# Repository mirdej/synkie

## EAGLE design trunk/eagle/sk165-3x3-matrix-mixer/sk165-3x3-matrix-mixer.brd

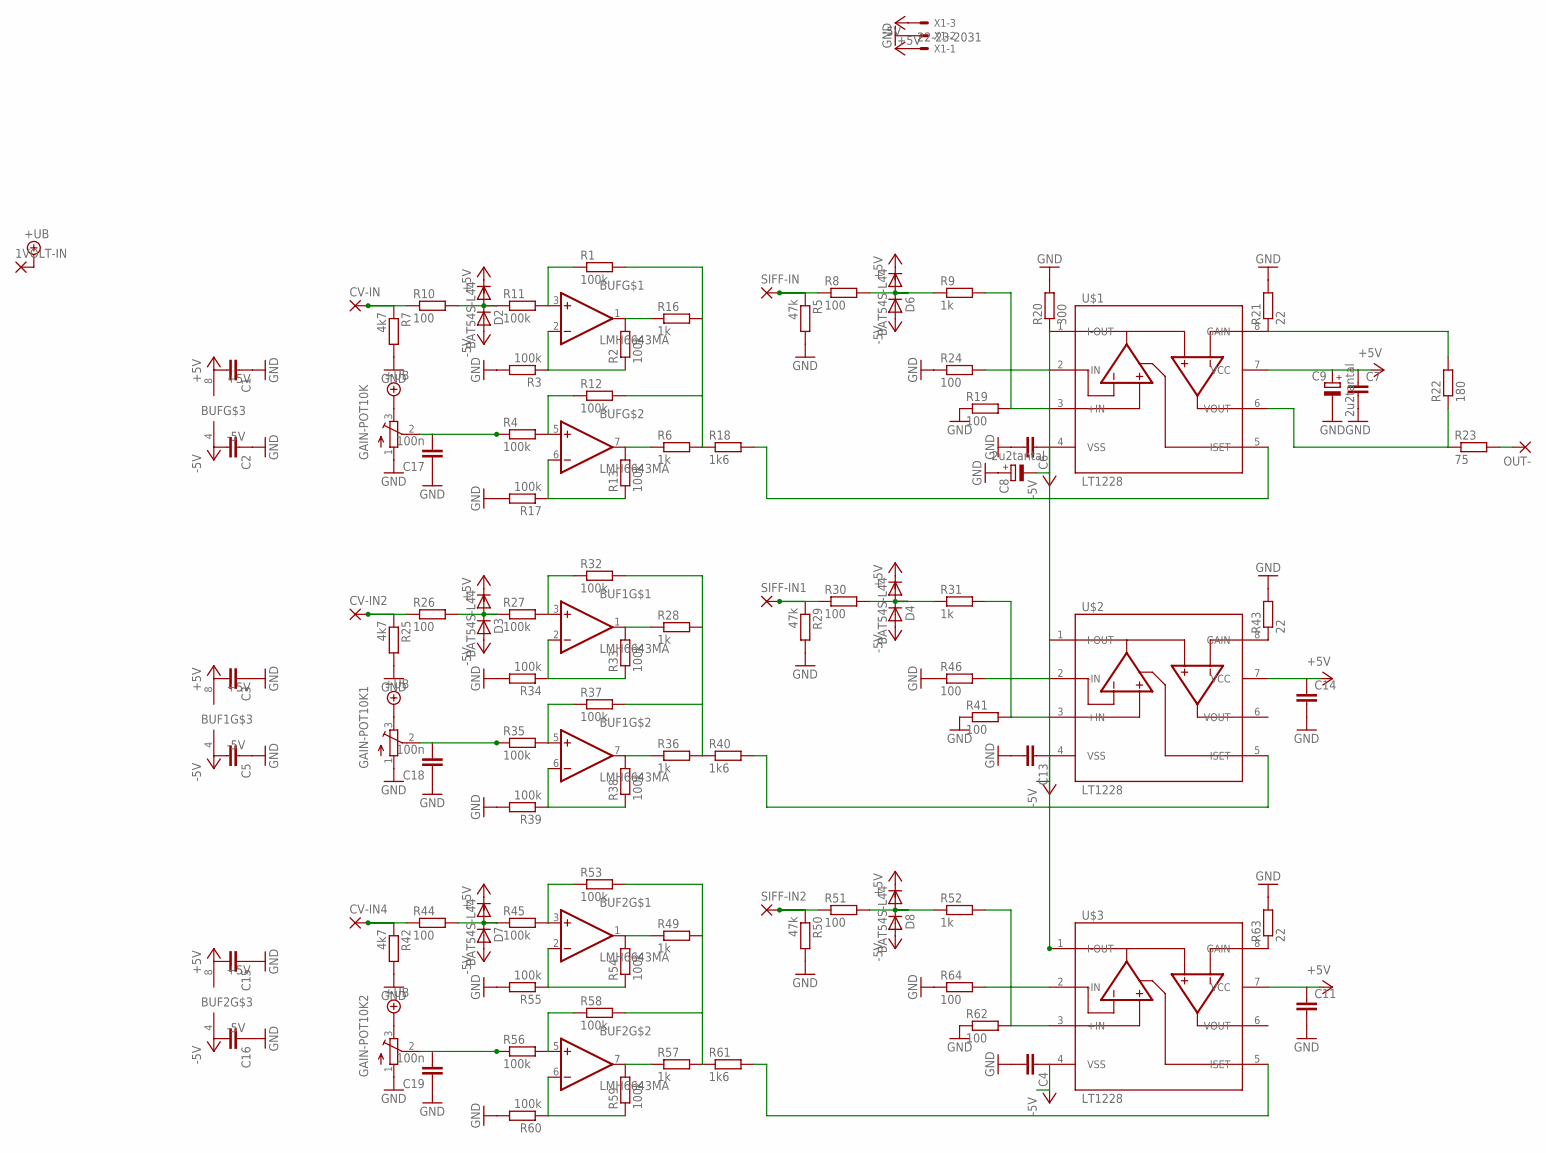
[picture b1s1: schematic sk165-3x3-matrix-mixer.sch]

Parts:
1VOLT-IN: 3,17/1,1
BUF, BUF1, BUF2: LMH6643MA; SO08
C1, C2, C3, C4, C5, C6, C7, C11, C13, C14, C15, C16: C-EUC1206; C1206
C8, C9: 2u2tantal; CT6032
C17, C18, C19: 100n; C1206
CV-IN, CV-IN2, CV-IN4: 3,17/1,1
D2, D3, D4, D6, D7, D8: BAT54S-L44; SOT23
GAIN-POT10K, GAIN-POT10K1, GAIN-POT10K2: 10k; ALPS_RK09K111
OUT-: 3,17/1,1
R1, R2, R3, R4, R11, R12, R13, R17, R27, R32, R33, R34, R35, R37, R38, R39, R45, R53, R54, R55, R56, R58, R59, R60: 100k; R1206
R5, R29, R50: 47k; R1206
R6, R9, R16, R28, R31, R36, R49, R52, R57: 1k; R1206
R7, R25, R42: 4k7; R1206
R8, R10, R19, R24, R26, R30, R41, R44, R46, R51, R62, R64: 100; R1206
R18, R40, R61: 1k6; R1206
R20: 300; R1206
R21, R43, R63: 22; R1206
R22: 180; R1206
R23: 75; R1206
SIFF-IN, SIFF-IN1, SIFF-IN2: 3,17/1,1
U$1, U$2, U$3: LT1228; SO08
X1: 22-23-2031

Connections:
+5V: BUF.8 (+5V), BUF1.8 (+5V), BUF2.8 (+5V), C1.2, C3.2, C7.1, C9.+, C11.1, C14.1, C15.2, D2.2 (C), D3.2 (C), D4.2 (C), D6.2 (C), D7.2 (C), D8.2 (C), U$1.7 (VCC), U$2.7 (VCC), U$3.7 (VCC), X1.3
+UB: 1VOLT-IN.1, GAIN-POT10K.3 (E), GAIN-POT10K1.3 (E), GAIN-POT10K2.3 (E)
-5V: BUF.4 (-5V), BUF1.4 (-5V), BUF2.4 (-5V), C2.2, C4.1, C5.2, C6.1, C8.-, C13.1, C16.2, D2.1 (A), D3.1 (A), D4.1 (A), D6.1 (A), D7.1 (A), D8.1 (A), U$1.4 (VSS), U$2.4 (VSS), U$3.4 (VSS), X1.1
GND: C1.1, C2.1, C3.1, C4.2, C5.1, C6.2, C7.2, C8.+, C9.-, C11.2, C13.2, C14.2, C15.1, C16.1, C17.1, C18.1, C19.1, GAIN-POT10K.1 (S), GAIN-POT10K1.1 (S), GAIN-POT10K2.1 (S), R3.2, R5.2, R7.2, R17.2, R19.1, R20.2, R21.2, R24.1, R25.2, R29.2, R34.2, R39.2, R41.1, R42.2, R43.2, R46.1, R50.2, R55.2, R60.2, R62.1, R63.2, R64.1, X1.2
unnamed: C17.2, GAIN-POT10K.2 (W), R4.1
unnamed: C18.2, GAIN-POT10K1.2 (W), R35.1
unnamed: CV-IN2.1, R25.1, R26.1
unnamed: BUF.2 (-IN), R2.1, R3.1
unnamed: R9.2, R19.2, U$1.3 (+IN)
unnamed: CV-IN4.1, R42.1, R44.1
unnamed: BUF.5 (+IN), R4.2, R12.1
unnamed: BUF.7 (OUT), R6.1, R13.2
unnamed: R21.1, R22.2, U$1.8 (GAIN)
unnamed: CV-IN.1, R7.1, R10.1
unnamed: D2.3 (AC), R10.2, R11.1
unnamed: BUF.6 (-IN), R13.1, R17.1
unnamed: D3.3 (AC), R26.2, R27.1
unnamed: BUF.3 (+IN), R1.1, R11.2
unnamed: R5.1, R8.1, SIFF-IN.1
unnamed: D6.3 (AC), R8.2, R9.1
unnamed: BUF.1 (OUT), R2.2, R16.1
unnamed: R18.2, U$1.5 (ISET)
unnamed: R1.2, R6.2, R12.2, R16.2, R18.1
unnamed: R22.1, R23.1, U$1.6 (VOUT)
unnamed: OUT-.1, R23.2
unnamed: R24.2, U$1.2 (-IN)
unnamed: BUF1.3 (+IN), R27.2, R32.1
unnamed: BUF1.1 (OUT), R28.1, R33.2
unnamed: R28.2, R32.2, R36.2, R37.2, R40.1
unnamed: R29.1, R30.1, SIFF-IN1.1
unnamed: D4.3 (AC), R30.2, R31.1
unnamed: R31.2, R41.2, U$2.3 (+IN)
unnamed: BUF1.2 (-IN), R33.1, R34.1
unnamed: BUF1.5 (+IN), R35.2, R37.1
unnamed: BUF1.7 (OUT), R36.1, R38.2
unnamed: BUF1.6 (-IN), R38.1, R39.1
unnamed: R40.2, U$2.5 (ISET)
unnamed: R20.1, U$1.1 (I-OUT), U$2.1 (I-OUT), U$3.1 (I-OUT)
unnamed: D7.3 (AC), R44.2, R45.1
unnamed: BUF2.3 (+IN), R45.2, R53.1
unnamed: BUF2.1 (OUT), R49.1, R54.2
unnamed: R46.2, U$2.2 (-IN)
unnamed: C19.2, GAIN-POT10K2.2 (W), R56.1
unnamed: R49.2, R53.2, R57.2, R58.2, R61.1
unnamed: R43.1, U$2.8 (GAIN)
unnamed: R50.1, R51.1, SIFF-IN2.1
unnamed: D8.3 (AC), R51.2, R52.1
unnamed: R52.2, R62.2, U$3.3 (+IN)
unnamed: BUF2.2 (-IN), R54.1, R55.1
unnamed: BUF2.5 (+IN), R56.2, R58.1
unnamed: BUF2.7 (OUT), R57.1, R59.2
unnamed: BUF2.6 (-IN), R59.1, R60.1
unnamed: R61.2, U$3.5 (ISET)
unnamed: R64.2, U$3.2 (-IN)
unnamed: R63.1, U$3.8 (GAIN)

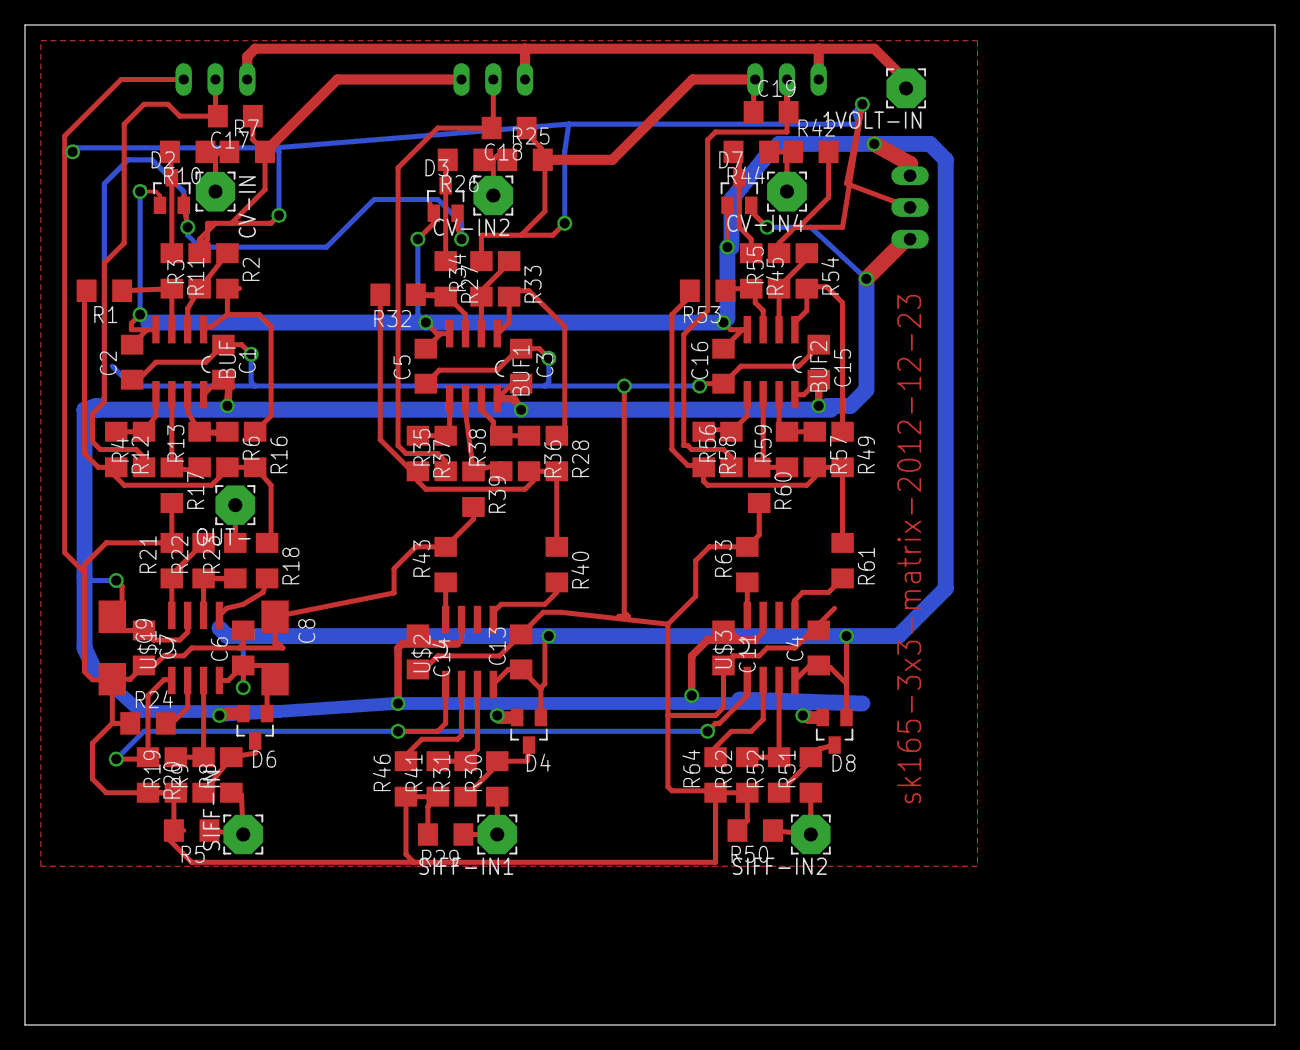
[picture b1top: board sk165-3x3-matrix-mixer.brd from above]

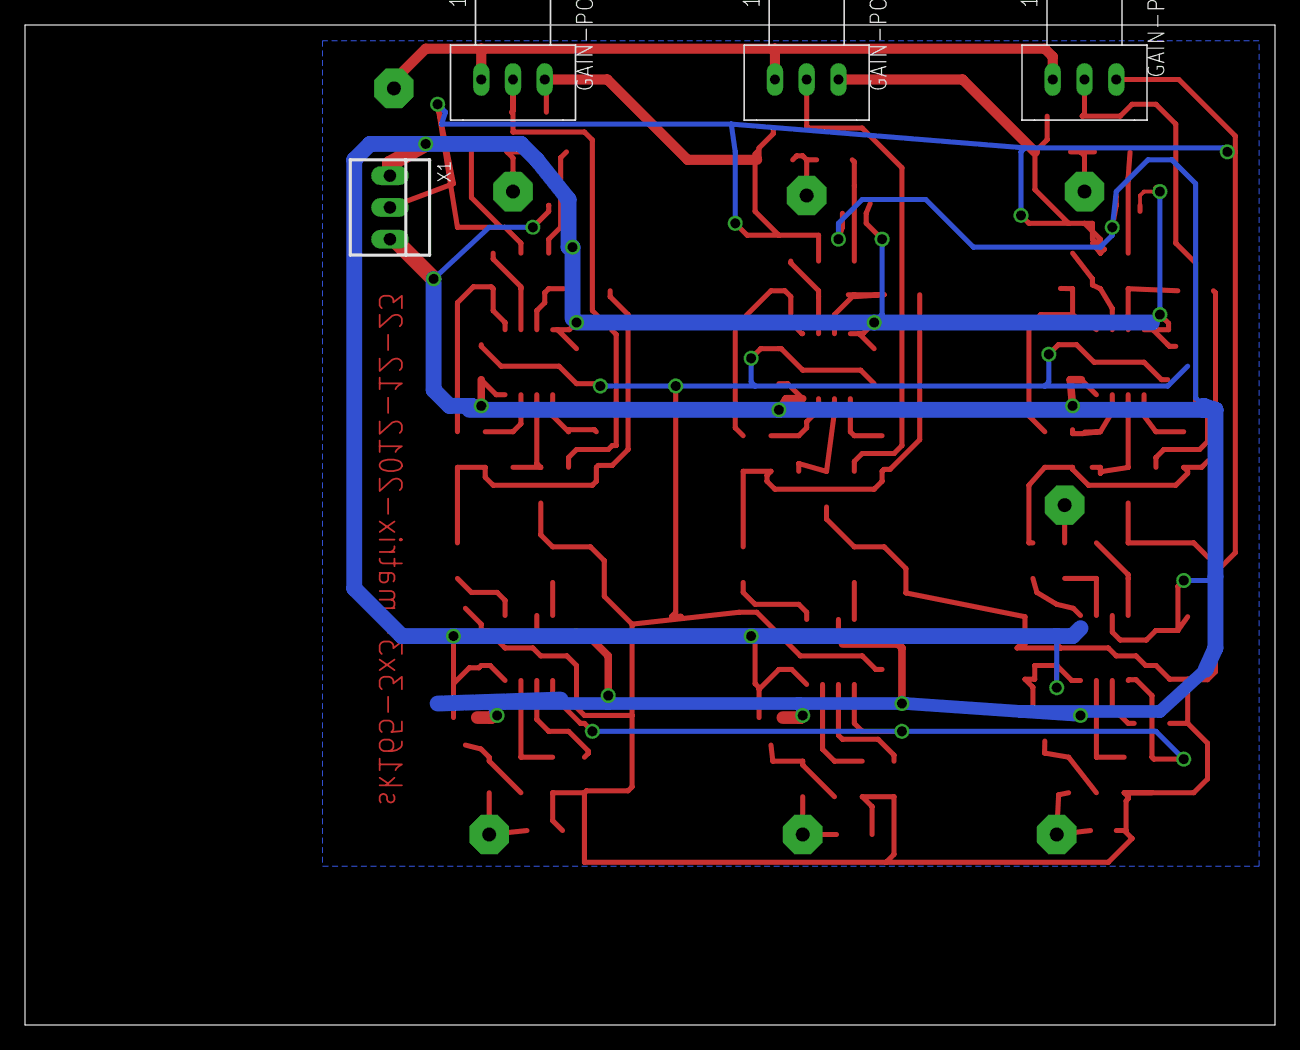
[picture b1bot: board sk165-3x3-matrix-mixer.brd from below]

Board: 2 copper layers, 100.0 x 80.0 mm, 101 parts (4 on the bottom side), 55 nets.

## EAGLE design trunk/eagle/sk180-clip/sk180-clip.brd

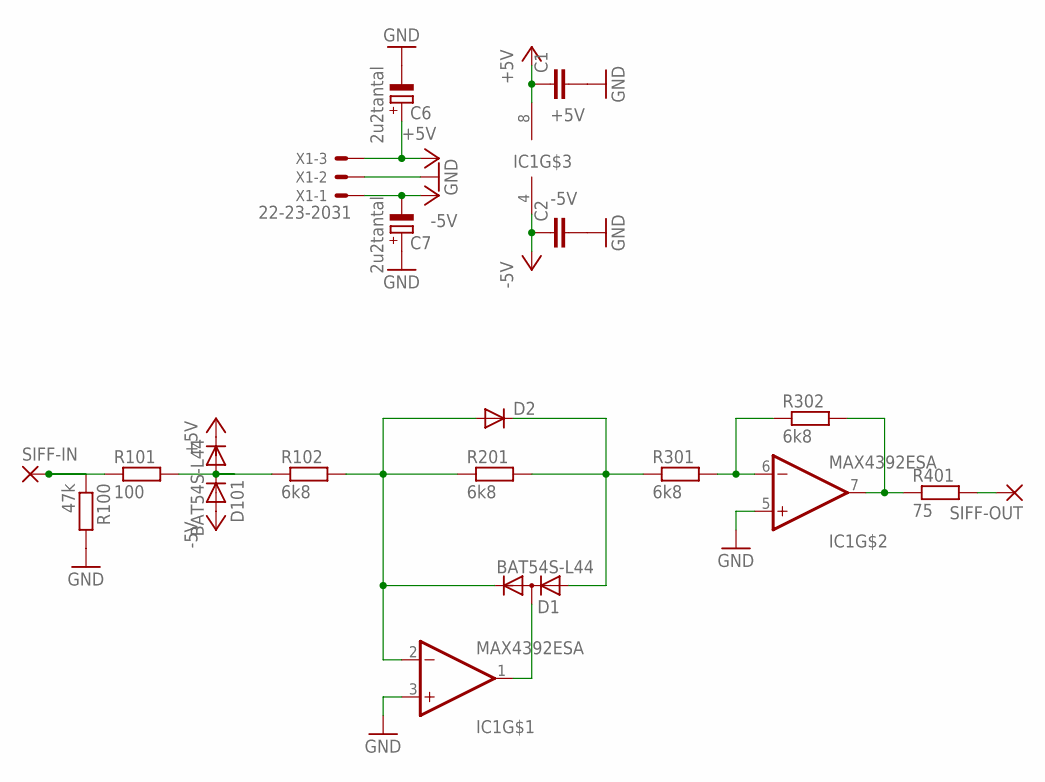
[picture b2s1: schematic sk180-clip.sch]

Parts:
C1, C2: C-EUC1206; C1206
C6, C7: 2u2tantal; CT3528
D1, D101: BAT54S-L44; SOT23
D2: DIODE-MINIMELF; MINIMELF
IC1: MAX4392ESA; SO08
R100: 47k; R1206
R101: 100; R1206
R102, R201, R301, R302: 6k8; R1206
R401: 75; R1206
SIFF-IN: 3,17/1,1
SIFF-OUT: 3,17/1,1
X1: 22-23-2031

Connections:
+5V: C1.1, C6.+, D101.2 (C), IC1.8 (+5V), X1.3
-5V: C2.1, C7.-, D101.1 (A), IC1.4 (-5V), X1.1
GND: C1.2, C2.2, C6.-, C7.+, IC1.3 (+IN), IC1.5 (+IN), R100.2, X1.2
unnamed: D1.2 (C), D2.A, IC1.2 (-IN), R102.2, R201.1
unnamed: D1.3 (AC), IC1.1 (OUT)
unnamed: D1.1 (A), D2.C, R201.2, R301.1
unnamed: IC1.6 (-IN), R301.2, R302.1
unnamed: IC1.7 (OUT), R302.2, R401.1
unnamed: R401.2, SIFF-OUT.1
unnamed: R100.1, R101.1, SIFF-IN.1
unnamed: D101.3 (AC), R101.2, R102.1

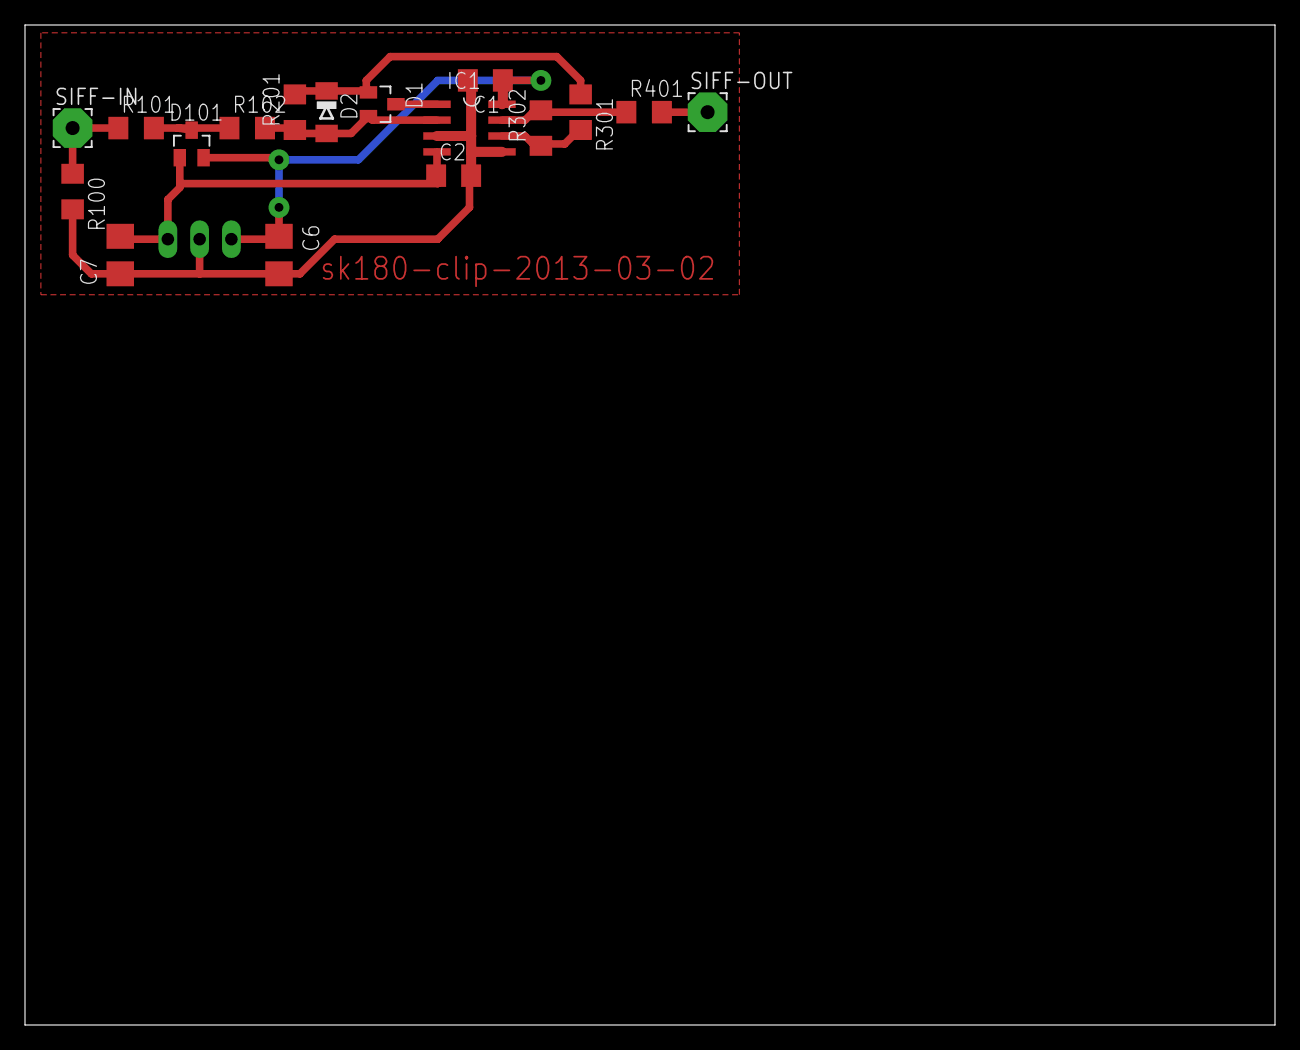
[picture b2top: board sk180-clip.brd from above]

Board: 2 copper layers, 100.0 x 80.0 mm, 18 parts (1 on the bottom side), 11 nets.

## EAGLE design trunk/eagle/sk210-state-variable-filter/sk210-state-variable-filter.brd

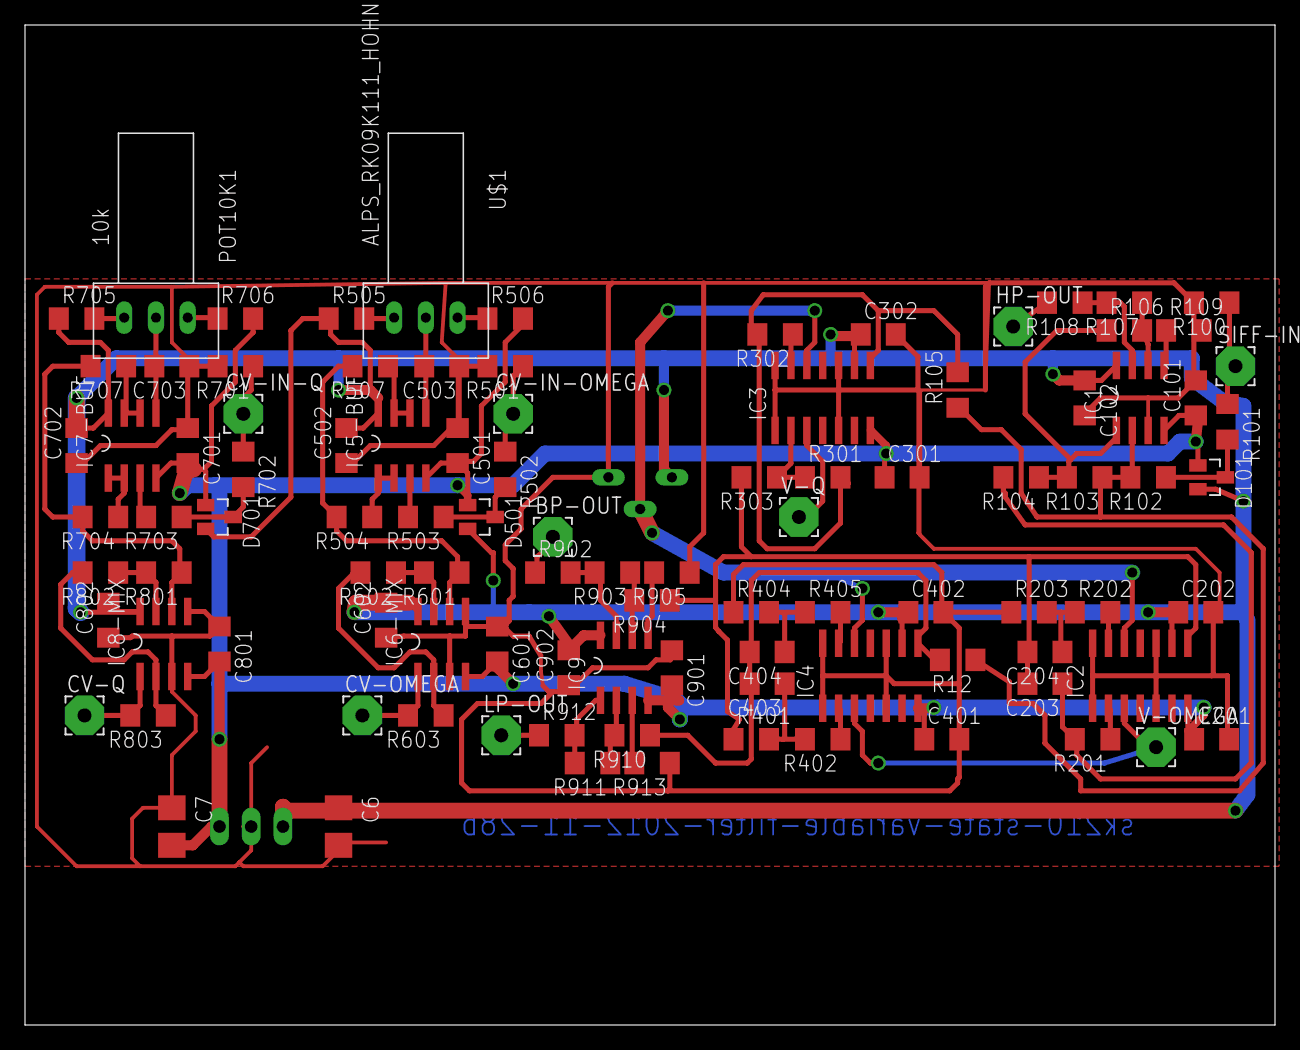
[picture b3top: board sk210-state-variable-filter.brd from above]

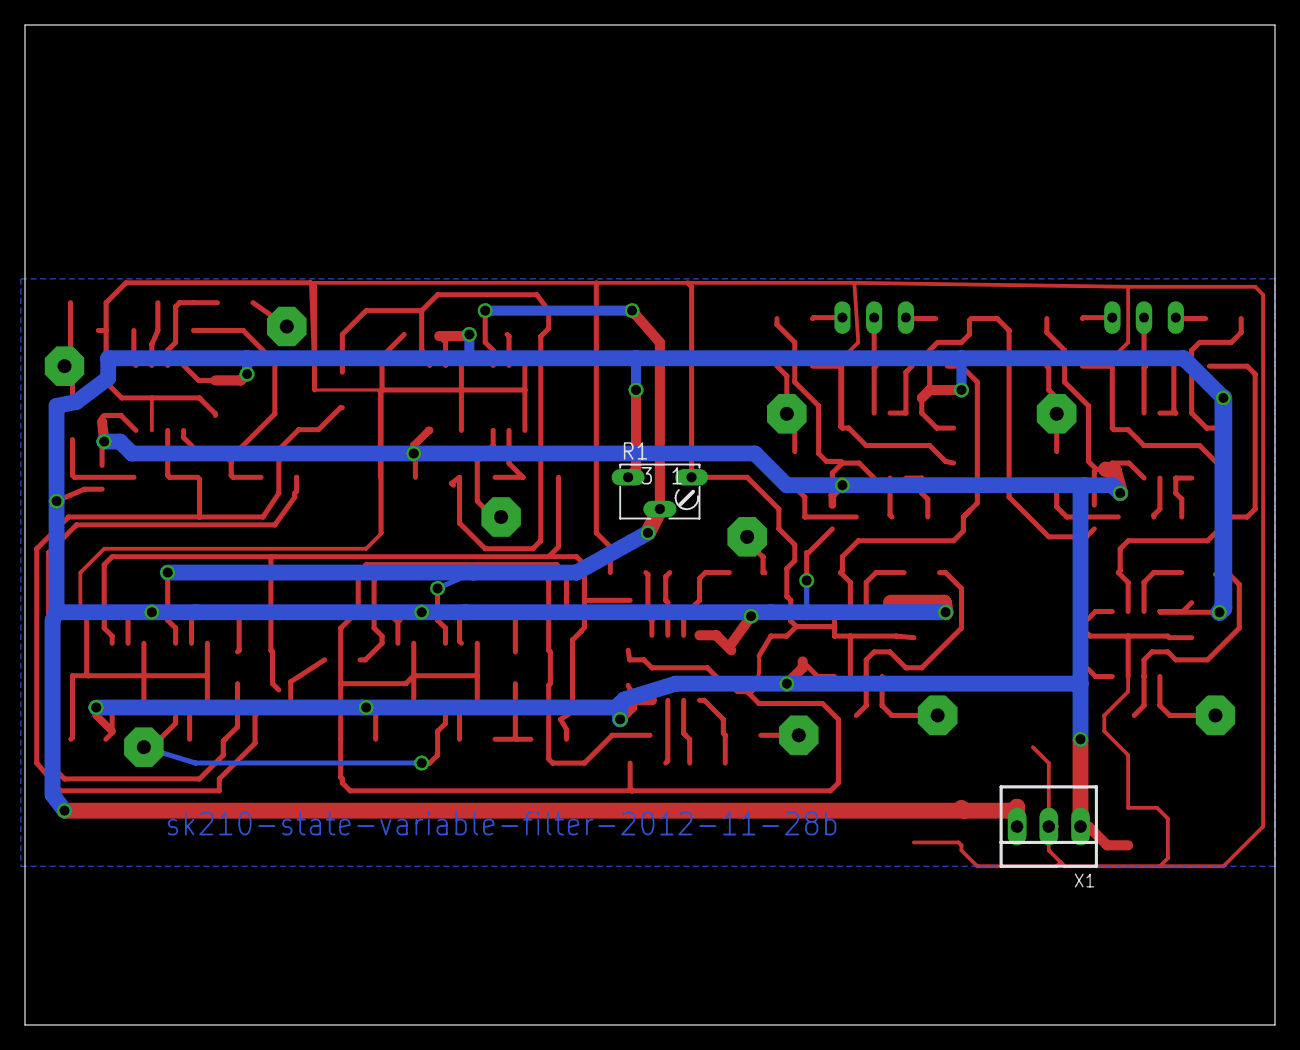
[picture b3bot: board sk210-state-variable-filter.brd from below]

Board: 2 copper layers, 100.0 x 80.0 mm, 101 parts (2 on the bottom side), 59 nets.

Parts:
BP-OUT: 3,17/1,1
C6, C7: 2u2tantal; CT3528
C101, C102, C501, C502, C601, C602, C701, C702, C801, C802, C901, C902: C1206
C201, C202, C301, C302, C401, C402, C503, C703: 100n; C1206
C203, C204, C403, C404: 120p; C1206
CV-IN-OMEGA: 3,17/1,1
CV-IN-Q: 3,17/1,1
CV-OMEGA: 3,17/1,1
CV-Q: 3,17/1,1
D101, D501, D701: BAT54S-L44; SOT23
HP-OUT: 3,17/1,1
IC1, IC5-BUF, IC6-MIX, IC7-BUF, IC8-MIX, IC9: MAX4392ESA; SO08
IC2, IC3, IC4: LT1256; SO14
LP-OUT: 3,17/1,1
POT10K1: 10k; ALPS_RK09K111
R1: B64W
R12, R102, R103, R104, R106, R107, R203, R401, R404, R903, R904, R910, R911: 1k; R1206
R100, R501, R701: 47k; R1206
R101, R502, R503, R702, R703: 100; R1206
R105, R109, R905, R913: 500; R1206
R108, R902, R912: 75; R1206
R201, R202, R301, R302, R303, R402, R405: 1k5; R1206
R504, R507, R601, R602, R603, R704, R707, R801, R802, R803: 6k8; R1206
R505, R506, R705, R706: 20k; R1206
SIFF-IN: 3,17/1,1
U$1: ALPS_RK09K111_HOHNE-FüSSE; ALPS_RK09K111
V-OMEGA: 3,17/1,1
V-Q: 3,17/1,1
X1: 22-23-2031

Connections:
+5V: C6.+, C102.1, C202.1, C302.1, C402.1, C502.2, C602.2, C702.2, C802.2, C902.2, D101.2, D501.2, D701.2, IC1.8, IC2.9, IC3.9, IC4.9, IC5-BUF.8, IC6-MIX.8, IC7-BUF.8, IC8-MIX.8, IC9.8, R1.E, R505.1, R705.1, X1.3
+UB: IC2.12, IC3.12, IC4.12, R1.S
-5V: C7.-, C101.1, C201.1, C301.1, C401.1, C501.2, C601.2, C701.2, C801.2, C901.2, D101.1, D501.1, D701.1, IC1.4, IC2.7, IC3.7, IC4.7, IC5-BUF.4, IC6-MIX.4, IC7-BUF.4, IC8-MIX.4, IC9.4, R506.2, R706.2, X1.1
GND: C6.-, C7.+, C101.2, C102.2, C201.2, C202.2, C301.2, C302.2, C401.2, C402.2, C501.1, C502.1, C503.1, C601.1, C602.1, C701.1, C702.1, C703.1, C801.1, C802.1, C901.1, C902.1, IC1.3, IC2.1, IC2.5, IC2.10, IC2.14, IC3.1, IC3.5, IC3.10, IC3.14, IC4.1, IC4.5, IC4.10, IC4.14, IC6-MIX.3, IC6-MIX.5, IC8-MIX.3, IC8-MIX.5, R1.A, R100.2, R109.2, R203.1, R404.1, R501.2, R701.2, R905.1, R913.1, X1.2
unnamed: C503.2, IC5-BUF.5, U$1.2
unnamed: R506.1, U$1.1
unnamed: R505.2, U$1.3
unnamed: IC1.7, R107.2, R108.1
unnamed: IC1.2, R12.1, R102.2, R103.1, R105.1
unnamed: C203.1, R104.2, R201.2
unnamed: C203.2, C204.2, IC2.8, R303.2, R401.1, R904.1
unnamed: IC3.2, R301.1, R303.1
unnamed: IC3.8, R105.2, R301.2, R302.2
unnamed: CV-IN-OMEGA.1, R501.1, R502.1
unnamed: D501.3, R502.2, R503.1
unnamed: IC2.2, R201.1
unnamed: IC5-BUF.6, IC5-BUF.7, R507.1
unnamed: IC5-BUF.3, R503.2
unnamed: R100.1, R101.1, SIFF-IN.1
unnamed: D101.3, R101.2, R102.1
unnamed: IC5-BUF.1, IC5-BUF.2, R504.1
unnamed: IC3.13, R302.1
unnamed: IC6-MIX.6, R504.2, R507.2, R601.1
unnamed: IC6-MIX.7, R601.2, R602.1
unnamed: IC6-MIX.2, R602.2, R603.1
unnamed: CV-OMEGA.1, IC6-MIX.1, R603.2
unnamed: IC3.3, V-Q.1
unnamed: IC2.3, IC4.3, V-OMEGA.1
unnamed: CV-IN-Q.1, R701.1, R702.1
unnamed: IC2.13, R202.2
unnamed: C204.1, R202.1, R203.2
unnamed: C403.1, R401.2, R402.2
unnamed: C403.2, C404.2, IC4.8, R12.2, R910.1
unnamed: IC4.2, R402.1
unnamed: D701.3, R702.2, R703.1
unnamed: C404.1, R404.2, R405.1
unnamed: IC7-BUF.3, R703.2
unnamed: IC7-BUF.1, IC7-BUF.2, R704.1
unnamed: IC7-BUF.6, IC7-BUF.7, R707.1
unnamed: IC8-MIX.6, R704.2, R707.2, R801.1
unnamed: IC8-MIX.7, R801.2, R802.1
unnamed: IC8-MIX.2, R802.2, R803.1
unnamed: CV-Q.1, IC8-MIX.1, R803.2
unnamed: C703.2, IC7-BUF.5, POT10K1.2
unnamed: POT10K1.1, R706.1
unnamed: POT10K1.3, R705.2
unnamed: IC9.1, R911.2, R912.2
unnamed: HP-OUT.1, R108.2
unnamed: IC9.7, R902.2, R903.2
unnamed: IC1.1, R103.2, R104.1, R106.1
unnamed: LP-OUT.1, R912.1
unnamed: BP-OUT.1, R902.1
unnamed: IC9.6, R903.1, R904.2
unnamed: IC9.5, R905.2
unnamed: IC1.6, R106.2, R107.1
unnamed: IC1.5, R109.1
unnamed: IC9.2, R910.2, R911.1
unnamed: IC9.3, R913.2
R403: IC4.13, R405.2

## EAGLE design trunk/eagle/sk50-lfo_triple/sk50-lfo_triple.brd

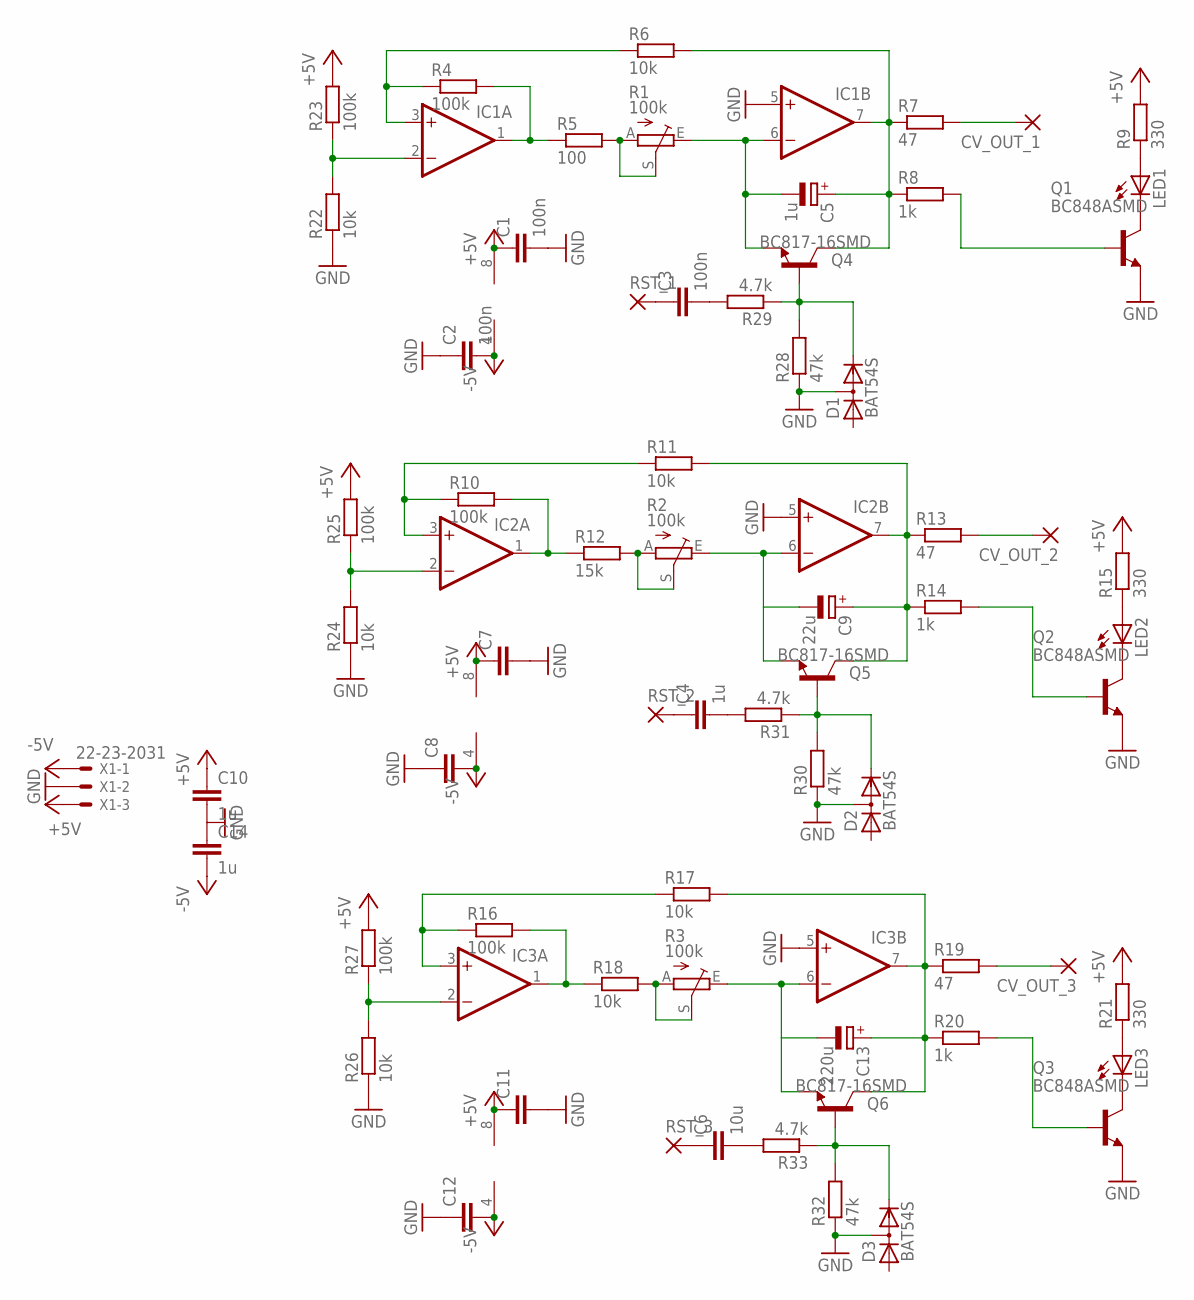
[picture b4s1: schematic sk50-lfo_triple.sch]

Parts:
C1, C2, C3: 100n; C1206
C4, C10, C14: 1u; C1206
C5: 1u; E2,5-5
C6: 10u; C1206
C7, C8, C11, C12: C-EUC1206; C1206
C9: 22u; E2,5-5
C13: 220u; E2,5-5
CV_OUT_1, CV_OUT_2, CV_OUT_3: 3,17/1,1
D1, D2, D3: BAT54S; SOT23
IC1, IC2, IC3: 2AMP_P8+4D; SO08
LED1, LED2, LED3: LED3MM
Q1, Q2, Q3: BC848ASMD; SOT23
Q4, Q5, Q6: BC817-16SMD; SOT23-BEC
R1, R2, R3: 100k; CIP20C-6MM
R4, R10, R16, R23, R25, R27: 100k; R1206
R5: 100; R1206
R6, R11, R17, R18, R22, R24, R26: 10k; R1206
R7, R13, R19: 47; R1206
R8, R14, R20: 1k; R1206
R9, R15, R21: 330; R1206
R12: 15k; R1206
R28, R30, R32: 47k; R1206
R29, R31, R33: 4.7k; R1206
RST_1, RST_2, RST_3: 3,17/1,1
X1: 22-23-2031

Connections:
+5V: C1.1, C7.1, C10.1, C11.1, IC1.8 (V+), IC2.8 (V+), IC3.8 (V+), R9.2, R15.2, R21.2, R23.2, R25.2, R27.2, X1.3
-5V: C2.2, C8.2, C12.2, C14.2, IC1.4 (V-), IC2.4 (V-), IC3.4 (V-), X1.1
GND: C1.2, C2.1, C7.2, C8.1, C10.2, C11.2, C12.1, C14.1, D1.3 (AC), D2.3 (AC), D3.3 (AC), IC1.5 (+IN), IC2.5 (+IN), IC3.5 (+IN), Q1.2 (E), Q2.2 (E), Q3.2 (E), R22.1, R24.1, R26.1, R28.1, R30.1, R32.1, X1.2
unnamed: IC1.3 (+IN), R4.1, R6.1
unnamed: IC1.1 (OUT), R4.2, R5.1
unnamed: R1.A, R1.S, R5.2
unnamed: C5.-, IC1.6 (-IN), Q4.E, R1.E
unnamed: C5.+, IC1.7 (OUT), Q4.C, R6.2, R7.1, R8.1
unnamed: LED2.A, R15.1
unnamed: CV_OUT_1.1, R7.2
unnamed: Q1.1 (B), R8.2
unnamed: LED1.A, R9.1
unnamed: LED1.K (C), Q1.3 (C)
unnamed: IC2.3 (+IN), R10.1, R11.1
unnamed: IC2.1 (OUT), R10.2, R12.1
unnamed: R2.A, R2.S, R12.2
unnamed: C9.-, IC2.6 (-IN), Q5.E, R2.E
unnamed: C9.+, IC2.7 (OUT), Q5.C, R11.2, R13.1, R14.1
unnamed: LED2.K (C), Q2.3 (C)
unnamed: CV_OUT_2.1, R13.2
unnamed: Q2.1 (B), R14.2
unnamed: LED3.A, R21.1
unnamed: LED3.K (C), Q3.3 (C)
unnamed: IC3.3 (+IN), R16.1, R17.1
unnamed: IC3.1 (OUT), R16.2, R18.1
unnamed: R3.A, R3.S, R18.2
unnamed: C13.-, IC3.6 (-IN), Q6.E, R3.E
unnamed: C13.+, IC3.7 (OUT), Q6.C, R17.2, R19.1, R20.1
unnamed: Q3.1 (B), R20.2
unnamed: CV_OUT_3.1, R19.2
unnamed: IC1.2 (-IN), R22.2, R23.1
unnamed: IC2.2 (-IN), R24.2, R25.1
unnamed: IC3.2 (-IN), R26.2, R27.1
unnamed: C3.2, R29.2
unnamed: C3.1, RST_1.1
unnamed: D2.2 (C), Q5.B, R30.2, R31.1
unnamed: D1.2 (C), Q4.B, R28.2, R29.1
unnamed: C4.2, R31.2
unnamed: C6.2, R33.2
unnamed: C4.1, RST_2.1
unnamed: C6.1, RST_3.1
unnamed: D3.2 (C), Q6.B, R32.2, R33.1

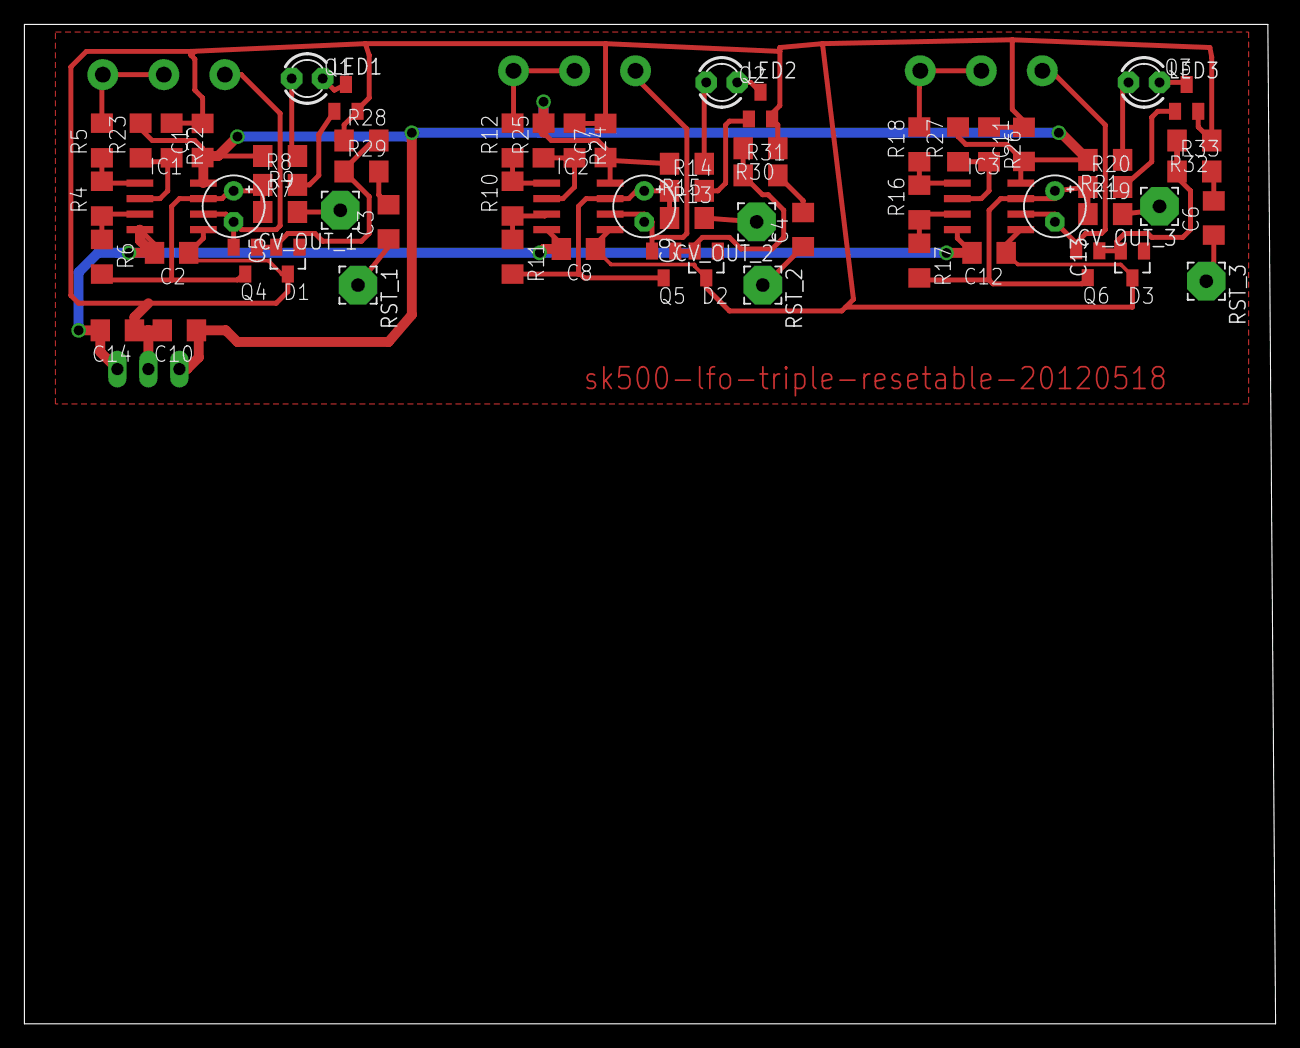
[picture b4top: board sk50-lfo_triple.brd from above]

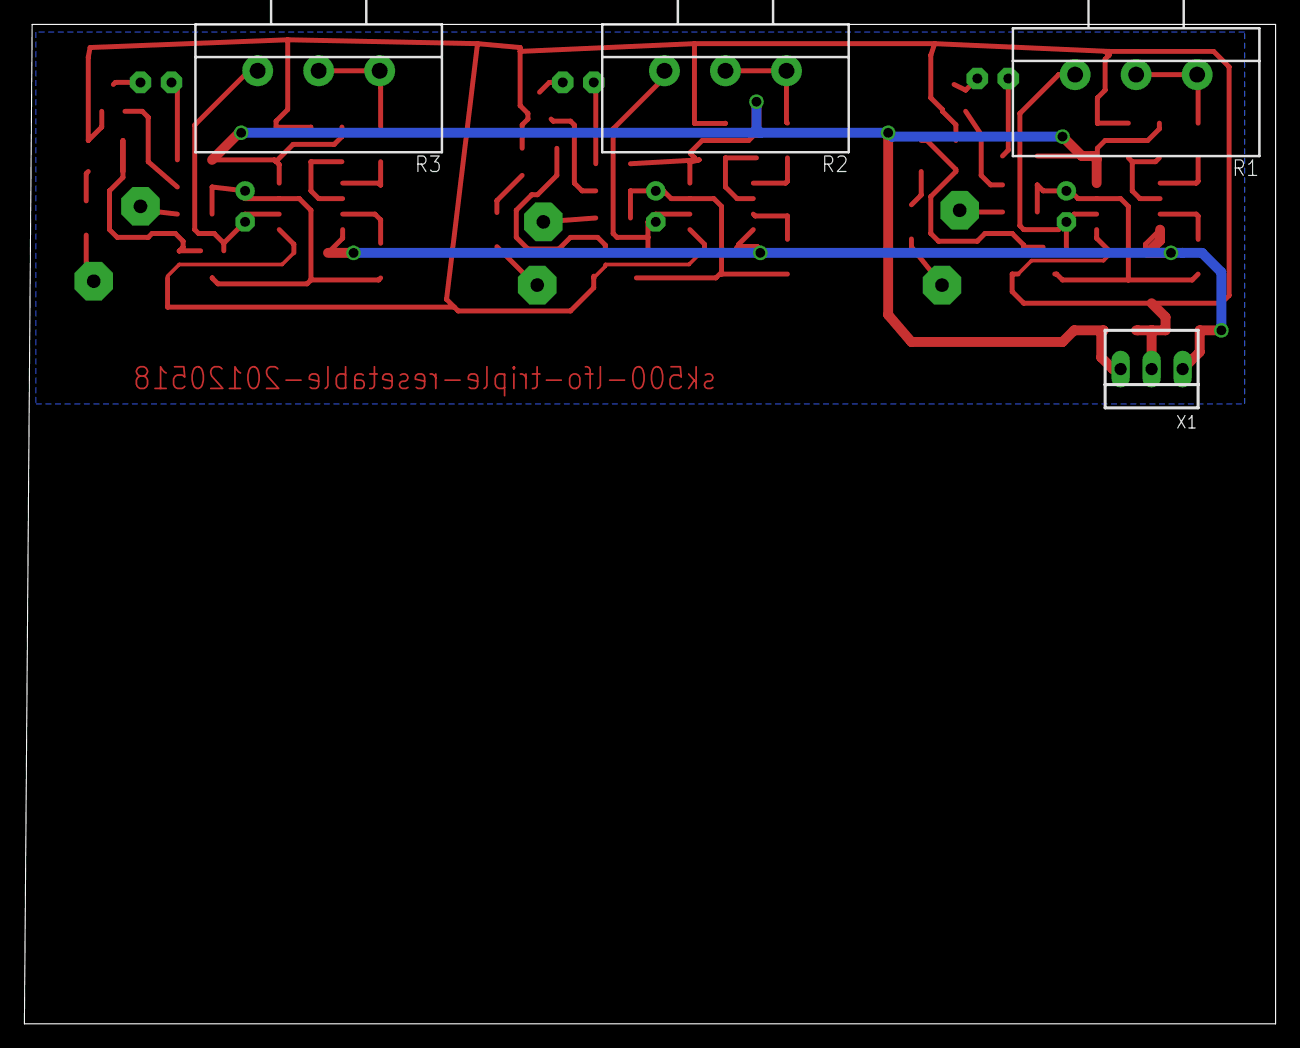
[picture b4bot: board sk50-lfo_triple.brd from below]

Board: 2 copper layers, 102.5 x 81.9 mm, 69 parts (4 on the bottom side), 42 nets.
